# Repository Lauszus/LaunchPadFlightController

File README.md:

# LaunchPad Flight Controller
#### Developed by Kristian Sloth Lauszus, 2015-2020
_________

This is a flight controller used for a quadcopter in X-configuration.

It is written for the [Tiva C Series TM4C123G LaunchPad](http://www.ti.com/tool/EK-TM4C123GXL) running at 80 MHz.

More information can be found at the following blog posts: <http://blog.tkjelectronics.dk/2015/01/launchpad-flight-controller> and <http://blog.tkjelectronics.dk/2015/08/bachelors-thesis-launchpad-flight-controller>.

# Video demonstrations

Some video demonstrations of the flight controller can be seen at my [YouTube channel](https://www.youtube.com/playlist?list=PLRBI0ZWd8RfBnD1IZzrBdREjrzRAjWMqg).

# Report

The report I wrote for my Bachelor's thesis can be found in the [docs](docs) folder. The 3D model and Matlab code can be found in there as well.

# Features

* Rate mode, self level mode, heading hold and altitude hold
    - __AUX1:__ Use 3-POS switch for self level and heading hold. At first position both are off, at second position self level is on and at third position both are on
    - __AUX2:__ Use a 3-POS switch for altitude hold. Note that self level mode must be activated for altitude hold to work! At first position altitude hold is turned off, at second position altitude hold will use the distance measured using the sonar and/or LIDAR-Lite v3 and at the third position altitude hold will be using the altitude estimated using the barometer and accelerometer
* Store PID values, calibration values etc. in EEPROM
* Gyro, accelerometer & magnetometer calibration routine
    - Gyro is calibrated at startup
    - Accelerometer and magnetometer calibration routine can be activated in the code or by using the Android app
    - The magnetometer turns on the Blue LED while calibrating
        + Rotate flight controller slowly along all three axis
* Arm/disarm using rudder
* Status LEDs
* Supports CPPM receivers
* Gyro & accelerometer (MPU-6500 or MPU-9250)
* Magnetometer (HMC5883L or AK8963 (inside MPU-9250))
* Barometer (BMP180)
* Ultrasound sensor aka sonar (HC-SR04)
* [LIDAR-Lite v3](https://buy.garmin.com/en-US/US/p/557294)
    - Connect a 680 µF electrolytic capacitor from 5V to GND
* Optical flow sensor (ADNS3080)
* [Android application](https://github.com/Lauszus/LaunchPadFlightControllerAndroid)
* OneShot125 ESC support
* Buzzer feedback

# Current setup

* Motors: Dualsky 980kv
* ESC's: [Hobby King 20A ESC 3A UBEC (F-20A)](http://hobbyking.com/hobbyking/store/uh_viewItem.asp?idProduct=37253) - flashed with SimonK bs_nfet with OneShot125 and COMP_PWM = 1
* Propellers: 10x4.5
* Frame: [Hobby King Q450 V3 Glass Fiber Quadcopter Frame 450mm](http://hobbyking.com/hobbyking/store/__49725__Q450_V3_Glass_Fiber_Quadcopter_Frame_450mm_Integrated_PCB_Version.html)
* LiPo: [Turnigy 3300mAh 3S 30C Lipo Pack](http://hobbyking.com/hobbyking/store/uh_viewItem.asp?idProduct=35870)
* RX: [OrangeRX R615X](http://www.hobbyking.com/hobbyking/store/__46632__OrangeRx_R615X_Spektrum_JR_DSM2_DSMX_Compatible_6Ch_2_4GHz_Receiver_w_CPPM.html)
* TX: [Turnigy 9XR](http://www.hobbyking.com/hobbyking/store/__31544__Turnigy_9XR_Transmitter_Mode_2_No_Module_.html) flashed with OpenTX
* TX module: [OrangeRX 2.4GHz transmitter module](http://hobbyking.com/hobbyking/store/__24656__OrangeRX_DSMX_DSM2_2_4Ghz_Transmitter_Module_JR_Turnigy_compatible_.html)

# Pinout

| Pin  |        Connection       |   Hardware peripheral   |
|------|-------------------------|-------------------------|
| PA0  |         UART RX         |     U0RX (UART0 RX)     |
| PA1  |         UART TX         |     U0TX (UART0 TX)     |
| PA2  |         SPI CLK         |         SSI0CLK         |
| PA3  |         SPI SS          |         SSI0Fss         |
| PA4  |         SPI MISO        |         SSI0Rx          |
| PA5  |         SPI MOSI        |         SSI0Tx          |
| PA6  |           SCL           |         I2C1SCL         |
| PA7  |           SDA           |         I2C1SDA         |
| PB0* |       Bluetooth RX      |     U1RX (UART1 RX)     |
| PB1* |       Bluetooth TX      |     U1TX (UART1 TX)     |
| PB4  |         Motor 3         |         M0PWM2          |
| PB5  |         Motor 4         |         M0PWM3          |
| PB6  |         Motor 1         |         M0PWM0          |
| PB7  |         Motor 2         |         M0PWM1          |
| PC5  |        Sonar echo       |   WTimer0B (WT0CCP1)    |
| PC6  |        CPPM input       |   WTimer1A (WT1CCP0)    |
| PD2  |          Buzzer         |                         |
| PE0  |       Sonar trigger     |                         |
| PE1  |      ADNS3080 reset     |                         |
| PE2  |  MPU-6500/MPU-9250 INT  |                         |
| PE3  |       HMC5883L DRDY     |                         |
| PF0  |         Switch 1        |                         |
| PF1  |         Red LED         |                         |
| PF2  |        Blue LED         |                         |
| PF3  |        Green LED        |                         |
| PF4  |         Switch 2        |                         |

\* UART1 is connected to an HC-06 Bluetooth module running at a baudrate of 115200. __Not 5V tolerant!__, so make sure your Bluetooth module outputs 3.3 voltage level or use a logic level converter.

Furthermore WTimer1B is used to turn off motors if the connection to the RX is lost. SysTick counter is used for time basic time keeping functionality.

The MPU-6500/MPU-9250, HMC5883L, BMP180 and LIDAR-Lite v3 are connected via I<sup>2</sup>C if they are used.

All pins are defined in [src/Config.h](src/Config.h) and can be overriden by creating a file called "Config_custom.h" in the [src](src) directory allowing you to redefine the values.

# Notes

The motor layout follows the Naze32 in x-configuration i.e. motor 1 is bottom right, motor 2 is top right, motor 3 is bottom left and motor 4 is top left when looking from the back. Motor 1 and 4 should be spinning clockwise and motor 2 and 3 should be spinning counterclockwise.

Make sure that roll increases when tilting quadcopter to the right, pitch increases when pitching quadcopter upward and yaw increases when rotation quadcopter clockwise. This can be displayed using the graph menu in the [Android application](https://github.com/Lauszus/LaunchPadFlightControllerAndroid).

The flight controller is armed by having the throttle low and the rudder to the right. The flight controller is disarmed again by having the throttle low and the rudder to the left.

## Initial setup

1. Locate the line ```#define ONESHOT125 1``` in [PPM.c](src/PPM.c) and set line to 0 if your ESCs does not support OneShot125, if you are in doubt, then set the value to 0.
2. Configure the orientation of the MPU-9250/6500 and HMC5883L, so they corresponds to your setup. This is done inside ```mpu6500BoardOrientation``` and ```hmc5883lBoardOrientation``` in [MPU6500.c](src/MPU6500.c) and [HMC5883L.c](src/HMC5883L.c) respectively.
    * The x-axis should be facing forward, the y-axis should be facing to the right and the z-axis should be facing downward. Typically the axis is indicated on the breakout board for the sensor.

### Calibrating the ESCs

__WARNING:__ Take propellers OFF when testing and calibrating ESCs!!

In order calibrate the ESCs you need to do the following procedure:

1. Power up the board while holding down both hardware switches. The blue LED will come on, indicating that the ESCs will be calibrated at next power up.
2. Turn the board off by disconnecting the battery.
3. Now apply power while holding down the two hardware switches. The board will send out the maximum and minimum pulses to the ESCs and thus calibrating them. When the ESC calibration is done the blue LED will be turned off and a long beep will be played.

The calibration is canceled if the buttons are not held down during the whole procedure or the reset is not performed by a power on reset. The former allows the user to cancel the calibration at any time by releasing the switches and the latter prevents the user from accidentally resetting the board without also resetting the ESCs, for instance by pressing the reset button on the board.

### Calibrating accelerometer and magnetometer

The last step is to calibrate the accelerometer and magnetometer. The accelerometer is calibrated by putting the quadcopter horizontal and activating the calibration routine via the [Android application's](https://github.com/Lauszus/LaunchPadFlightControllerAndroid) settings menu. It is important that the quadcopter is kept still while running the accelerometer calibration routine. When the calibration is done a long beep will be played using the onboard buzzer.

The magnetometer calibration routine is activated similar to the accelerometer by using the [Android application](https://github.com/Lauszus/LaunchPadFlightControllerAndroid). The blue LED will turn on, indicating that the calibration procedure is activated. Now rotate the quadcopter along all three axis slowly in order to find the minimum and maximum values. The user has 30 seconds to rotate the quadcopter. Once the calibration is done the blue LED will be turned off and a long beep will be played.

It is a good idea to confirm that the estimated angles are all correct by using the graph menu in the [Android application](https://github.com/Lauszus/LaunchPadFlightControllerAndroid).

There is no need to calibrate the gyroscope, as this is done at every startup.

### RX

The minimum and maximum receiver values are hardcoded in [src/Config.h](src/Config.h) and might need to be adjusted as well.

# Android application

The Android source code is available at the following repository: <https://github.com/Lauszus/LaunchPadFlightControllerAndroid>.

# GUI

A simple GUI can be found inside the [GUI](GUI) directory. It can be used to visualise the orientation of the flight controller.

# Build instructions

## PlatformIO

[PlatformIO](http://platformio.org) is a cross-platform build system, which makes it easy to compile and upload the code on both Windows, Linux and Mac. This is the recommended way to compile the code for novice users.

Please follow these instructions in order to install Python 2.7 and PlatformIO: <http://docs.platformio.org/en/latest/installation.html>.

On Windows be sure to select "Add python.exe to Path" when installing Python 2.7.

Open a terminal (search for ```cmd.exe``` on Windows) and navigate to the root of the project:

```bash
cd LaunchPadFlightController
```

Now compile the code:

```bash
platformio run
```

The program should now be compiled.

In order to upload the code simply type:

```bash
platformio run -t upload
```

I recommend installing the [PlatformIO IDE](http://platformio.org/get-started/ide?install) if using PlatformIO.

## Keil µVision IDE 5

In order to built this project you need to download Keil µVision IDE 5 and then simply open the [project file](LaunchPadFlightController.uvprojx).

## Manual installation

In order to built this project you will need to use [Make](http://www.gnu.org/software/make/).

First download and install [gcc-arm-none-eabi](https://launchpad.net/gcc-arm-embedded/4.8/4.8-2014-q3-update) and then install [lm4tools](https://github.com/utzig/lm4tools).

lm4tools can be installed like so:

```bash
$ git clone https://github.com/utzig/lm4tools.git
$ make -C lm4tools/lm4flash all
$ sudo cp lm4tools/lm4flash/lm4flash /usr/bin/
```

If you are on a Mac, I recommend installing gcc-arm-none-eabi using [Homebrew](http://brew.sh) like so:

```bash
$ brew tap PX4/homebrew-px4
$ brew update
$ brew install gcc-arm-none-eabi
```

Now simply compile the code by navigating to the [src](src) and running the following command:

```bash
make
```

And to upload the code:

```bash
make flash
```

Some information on configuring Eclipse for use with this project can be the [Wiki](https://github.com/Lauszus/LaunchPadFlightController/wiki).

### Hardware debugging using OpenOCD

OpenOCD can be installed via [Homebrew](http://brew.sh) as well:

```bash
$ brew install openocd
```

Now run the following commands:

```bash
$ openocd --file /usr/local/share/openocd/scripts/board/ek-tm4c123gxl.cfg

$ arm-none-eabi-gdb gcc/LaunchPadFlightController.axf
(gdb) target extended-remote :3333
(gdb) monitor reset halt
(gdb) load
(gdb) monitor reset init
```

More information regarding hardware debugging can be found at the [Wiki](https://github.com/Lauszus/LaunchPadFlightController/wiki/Hardware-Debugging-In-Eclipse).

# Credits

A lot of the inspiration for this code came from [Cleanflight](https://github.com/cleanflight/cleanflight) and other open source flight controller projects.

For more information send me an email at <lauszus@gmail.com>.

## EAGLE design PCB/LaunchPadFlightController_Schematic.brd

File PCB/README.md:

# LaunchPad Flight Controller
#### Developed by Kristian Sloth Lauszus, 2015
_________

This is the design files for the PCB that is designed to plug onto the headers on the Tiva LaunchPad. You can order the PCB directly from the following link: <https://www.oshpark.com/shared_projects/9DC5cp8e>.

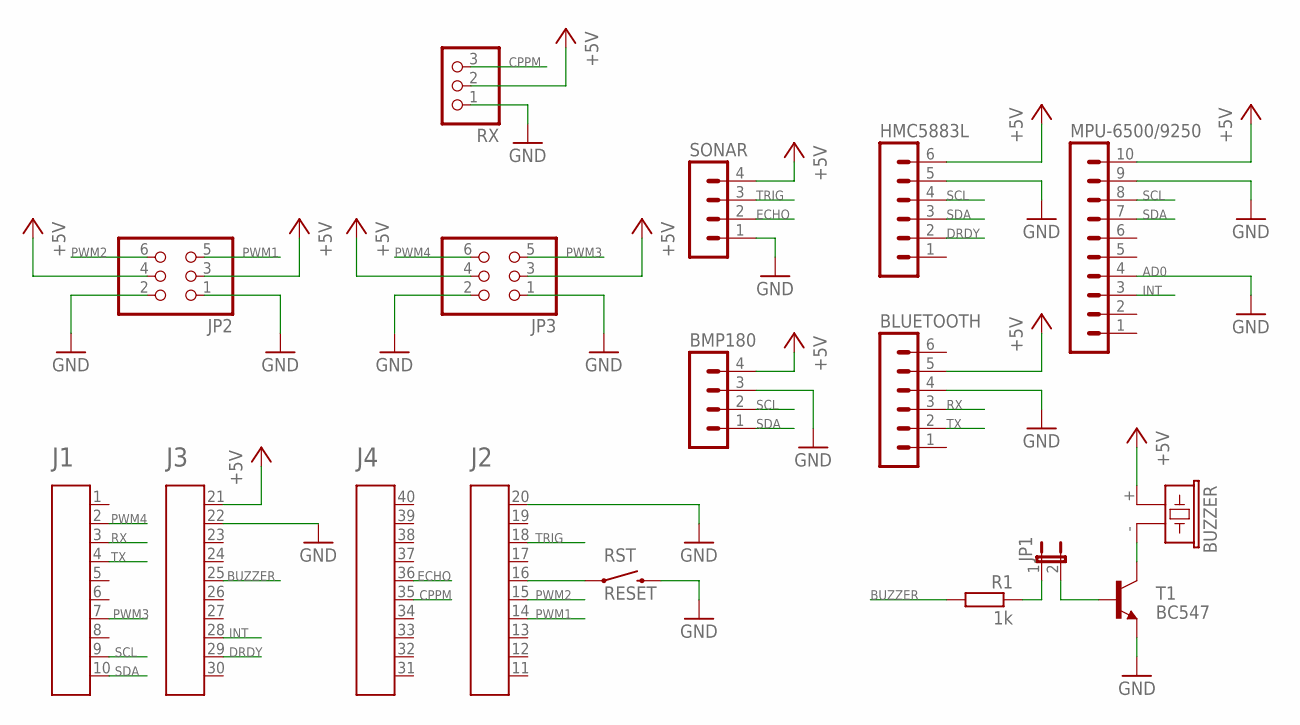
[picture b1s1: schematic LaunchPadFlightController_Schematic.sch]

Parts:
A1: HEADER4X10-BOOSTERPACK; 4X10-BOOSTERPACK
BLUETOOTH: MA06-1
BMP180: MA04-1
BUZZER: F/CM12P
HMC5883L: MA06-1
JP1: JP1E; JP1
JP2, JP3: PINHD-2X3; 2X03
MPU-6500/9250: MA10-1
R1: 1k; 0207/10
RST: RESET; TACTILE-PTH-EZ
RX: PINHD-1X3; 1X03
SONAR: MA04-1
T1: BC547; TO92

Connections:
+5V: A1.21, BLUETOOTH.5, BMP180.4, BUZZER.+ (1), HMC5883L.6, JP2.3, JP2.4, JP3.3, JP3.4, MPU-6500/9250.10, RX.2, SONAR.4
BUZZER: A1.25, R1.2
CPPM: A1.35, RX.3
DRDY: A1.29, HMC5883L.2
ECHO: A1.36, SONAR.2
GND: A1.20, A1.22, BLUETOOTH.4, BMP180.3, HMC5883L.5, JP2.1, JP2.2, JP3.1, JP3.2, MPU-6500/9250.4, MPU-6500/9250.9, RST.3 (2), RX.1, SONAR.1, T1.1 (E)
INT: A1.28, MPU-6500/9250.3
unnamed: A1.16, RST.1
unnamed: JP1.1, R1.1
unnamed: JP1.2, T1.2 (B)
unnamed: BUZZER.- (2), T1.3 (C)
PWM1: A1.14, JP2.5
PWM2: A1.15, JP2.6
PWM3: A1.7, JP3.5
PWM4: A1.2, JP3.6
RX: A1.3, BLUETOOTH.3
SCL: A1.9, BMP180.2, HMC5883L.4, MPU-6500/9250.8
SDA: A1.10, BMP180.1, HMC5883L.3, MPU-6500/9250.7
TRIG: A1.18, SONAR.3
TX: A1.4, BLUETOOTH.2

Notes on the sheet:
AD0

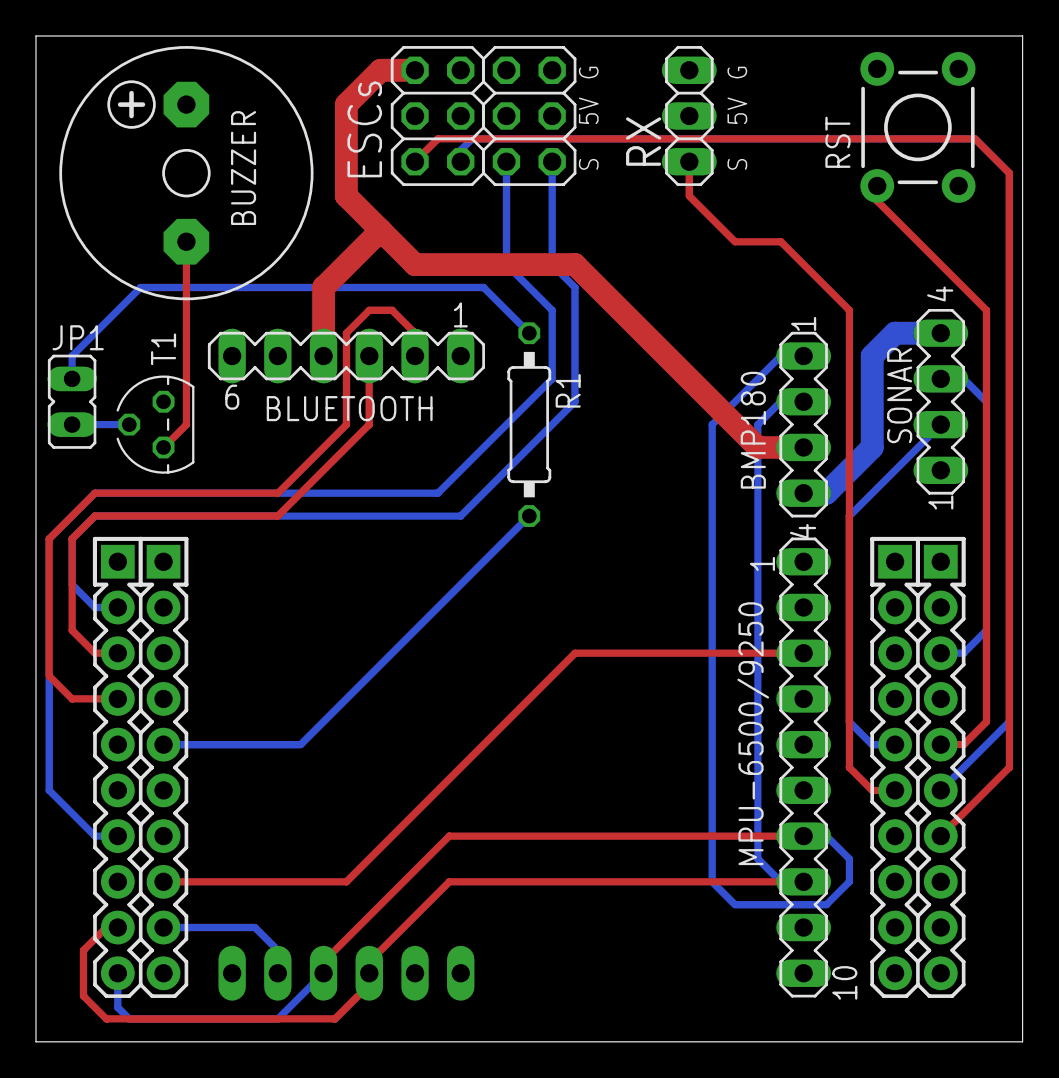
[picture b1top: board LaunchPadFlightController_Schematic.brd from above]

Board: 2 copper layers, 54.8 x 55.9 mm, 14 parts (1 on the bottom side), 20 nets.

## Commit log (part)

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2015-04-02 Check number of bytes available before calling UARTPeek1, as bytes might be received after UARTPeek1 is called
    There is still a slight change that data is received between the two functions, but it is very unlikely and the checksum should prevent the data to be actually stored
2015-04-05 Moved local variables into .c file
    Also save timer load value in variable
2015-04-05 Fix typo
2015-04-06 Can now set Angle Kp, maximum angle inclination and stick scaling
2015-04-08 Added buzzer code
2015-04-17 Updated TODO list
2015-04-17 Multiply PID values by a higher value to allow finer adjustments
2015-04-17 Take average of several deltas in D-term calculation
    Inspired by: https://github.com/cleanflight/cleanflight/blob/004dd0daaf5c89412064253f8549ebe1bfc03f99/src/main/flight/pid.c#L721-L732
2015-04-17 Beep for 1s after accelerometer calibration
2015-04-18 Can now calibrate accelerometer and restore default configuration values
    Nothing was changed in EEPROM.c except order of functions
2015-04-18 Only save Kp, Ki, Kd and integration limit in EEPROM
    There is no need to save the rest in the EEPROM
2015-04-18 Enabled OneShot125
    This allows the ESC output to be in sync with IMU reading.
    Note that motor update code was moved inside IMU reading code and some other code were rearranged - nothing else was changed in main.c
2015-04-18 Added list of current features
2015-04-18 Escape asterisk symbol
2015-04-19 Limit other motors if one reaches maximum
    Got code from: https://github.com/cleanflight/cleanflight/blob/78a4476506c06315d7296a010a2c7ba003146b44/src/main/flight/mixer.c#L680-L695
2015-04-22 Make sure UART_DEBUG is defined before printing debug information in RX.c
2015-04-22 Switch to Keil µVision IDE 5
2015-04-23 Improved self level mode
    Use rotation matrices to rotate accelerometer vector and use LPF on accelerometer values
    Inspired by: https://github.com/cleanflight/cleanflight/blob/78a4476506c06315d7296a010a2c7ba003146b44/src/main/flight/imu.c
    Doesn't seem like I can use my Kalman filter as it is, as it written for a 1-axis application
    Note I increase optimisation level to -O3 as well, as it generated wrong code at -O0
2015-04-23 Added GUI application used to visualise orientation of flight controller
    For now one has to manually set: https://github.com/Lauszus/LaunchPadFlightController/blob/2555673079926c2b7602c29a05033d63cc0e9e17/src/IMU.c#L85 to 1.
2015-04-24 Initial support for magnetometer (HMC5883L)
2015-04-24 Fix indentation
    No new code was added
2015-04-24 Moved magnetometer calibration routine into driver
2015-04-24 Send out angle information every 10 ms
    Also removed some unused code
2015-04-25 Don't hardcode register value, use name instead
2015-04-25 Added some information about Bluetooth module and magnetometer calibration routine
2015-04-25 Implemented heading hold mode
    Also found bug where angle mode were actually toggled back and forth instead of staying in angle mode
2015-04-27 Added credits
2015-04-28 Set accelerometer and gyroscope scale inside MPU-6500 driver
    This should make it easier to add support for other sensors in the future
2015-04-28 Make sure heading code is only compiled when magnetometer is actually used
    Also moved some variables into the relevant part of the code instead of being defined in the top
2015-04-28 New default angleKp value
2015-05-03 Fixed link to Android application and Cleanflight
2015-05-23 Almost got PlatformIO working
    Need to set reset handler and get it to compile the .S file.
2015-05-23 Initialise struct
    Fixes: "warning: 'mag_total.<U9098>.X' may be used uninitialized in this function [-Wmaybe-uninitialized]"
2015-05-23 Set optimisation level to -O3
2015-05-24 Added UART handlers to vector table
    Also increased stack size to match old one in startup_rvmdk.S
2015-05-25 Hardcode length of sensor buffer, so it compiles when using gcc
2015-05-25 math library should be lowercase
2015-05-25 New headKp value
2015-05-25 Move all rules onto one line
2015-05-25 Use object list to automatically build all object files
2015-05-25 Remove everything related to Kalman filter, as it is not used
2015-05-25 Don't hardcode target name
2015-05-25 Added space between variable name and value
2015-05-25 Print sizes of sections inside binary file
2015-05-25 Ignore Eclipse project files
2015-05-26 Added GDB commands notes
2015-05-26 Forgot to add '$' sign before commands
2015-05-26 Typo
2015-05-26 Normalize all the line endings
2015-05-26 Allow flags to be overridden by command line
    I use this with Eclipse
2015-05-26 Use state machine instead of delay, so the BMP180 driver can actually be used
2015-05-26 Also build versions with and without magnetometer and barometer enabled
2015-05-26 Set job manually, as matrix did not work
2015-05-26 Use one state less in BMP180 driver
2015-05-27 Added double-promotion and unsafe-loop-optimizations warnings
2015-05-27 Moved sonar to different pins
2015-05-27 Use temperature from BMP180 to compensate for the difference in speed of sound in air
2015-05-27 Implement altitude hold using sonar
2015-05-27 Return sonar distance in mm instead
2015-05-27 Reset alt hold terms separately
2015-05-27 There is no need to check if we should trigger sonar that often, so it is limited to the update rate of IMU
2015-05-27 Take care of timer overflow in a better way
2015-05-27 Added code, so sonar distance can easily be printed for debugging
2015-05-27 Don't turn on buzzer if timer overflows in DEBUG mode
2015-05-28 Only use '__attribute__((packed))' if it is actually needed in order to reduce code size
    Also added static keyword to some structs inside Bluetooth.c
2015-05-28 Added take off sequence
    Will take off and stay at 1m
2015-05-28 Added some comments in sonar driver
2015-05-28 Can now adjust height when in altitude mode
2015-05-28 Surround heading mode and altitude mode variables in #if statements
2015-05-28 Forgot to around altitudeMode variable in #if statement
2015-05-29 Not all code is released under GPL like all the TI files
2015-05-29 Altitude hold wan't properly reset
2015-05-29 Compensate for 3D tilt angle in sonar
2015-05-29 Just save US_ROUNDTRIP_CM as an integer, as mm resolution is more than what the sensor is capable of anyway
    Also updated some comments
2015-05-29 Moved altitude hold code into it's own source files
2015-05-29 Moved sonar code into altitude code as well
2015-05-29 Save maxAngleInclinationSonar in EEPROM
    Also made the it able to compile when USE_SONAR is 0
2015-05-29 Don't hardcode sonar minimum and maximum distance
2015-05-30 Fix so Bluetooth code compiles when no magnetometer is used
2015-05-30 Rename altitude hold file
2015-05-30 Surrond uartstdio.h include in if statements, so it throws an error if one try to print anyway
2015-05-30 Just pass temperature directly to sonar driver
2015-05-31 Make msg struct a local variable
2015-06-01 Added source files to Keil project file
2015-06-07 Removed unused include
2015-06-08 Go between 10cm to 50cm when checking altitude step response
2015-06-08 Show logging status using blue LED
2015-06-08 Set message length after checking if pointer is valid
2015-06-09 Added some more links about rotation matrices
2015-06-10 Updated Keil project file
2015-06-14 Added Android device art screenshots
2015-06-14 Added unused-parameter warning
2015-06-14 Use a different define variable to activate each step response code
2015-06-14 Rename variable, so it becomes more clear that it is in fact just a P controller
2015-06-15 There is no need to set altHoldSetPoint and altHoldInitialThrottle twice
2015-06-16 Deal with sonar overflow in a better way
    This is already dealt with in the altitude hold driver
2015-06-17 Suppress unused parameter warning
2015-06-17 Subtract sonar offset from all altitude estimates
2015-06-17 Renamed variable, so it is clear that it is the inertial frame
2015-06-18 Fixed comments and variable names as it is in the body frame and the altitude estimation should rotate it back into the inertial frame
2015-06-18 Added TODO
2015-06-18 Fixed comment
2015-06-18 Yaw angle is already inverted
2015-06-19 Magnetometer can also be calibrated using Android app
2015-06-21 Re-add overflow timer check in sonar driver
    I suspect that this is needed as the timer is operating as a 16-bit timer
2015-06-21 Renamed getAltitudeHold to getAltitude, so it better reflects what the code actually do
2015-07-06 Initial support for altitude hold based on barometer
2015-07-18 Fixed typo in BMP180 driver
2015-07-18 Added AK8963 driver
    The AK8963 is inside the MPU-9250
2015-07-18 Use the orientation function for the MPU-6500 inside the AK8963 driver
2015-07-18 Make getMagData return if new data is read
    This simplifies the mag calibration function
2015-07-23 Fixed debug print
2015-07-28 Cast sensor data explicitly to int16_t
    This was causing issues in the calibrateSensor function on some compilers, it was just done in the rest of the code to be future proof
2015-07-28 Stay in endless while loop if HMC5883L is detected, but self test fails
2015-07-29 Moved building instructions, GUI and Android sections down in the readme
2015-07-29 Added information about the report I wrote
2015-08-17 Print the type of magnetometer found inside high-level magnetometer driver instead
    LEDs had to be initialised before magnetomer was initialised, as the Blue LED will turn on in case no magnetometer is detected
2015-08-17 Added MPU-9250 to pinout table
2015-08-21 Uploaded PCB files
    Can be ordered here: https://oshpark.com/profiles/Lauszus
2015-08-23 Updated copyright header
2015-08-24 Added link to blog post
2015-09-07 Increased resolution of ADNS-3080 to 1600 counts per inch
    Also increased delay between printing pixel data to 1500 ms
2015-09-07 Always print leading with leading zeroes if value is less that two characters
2015-10-09 Added link to Wiki regarding hardware debugging
2016-01-18 Fixed a bunch of warnings
2016-04-22 Added changes to Keil configuration and file name issue.
2016-04-22 GUI file ajusted to Windows.
2016-04-23 MPU mounting direction corrected.
2016-04-26 msg_t already provide the length of the message
2016-04-28 Added READMEs for both the PCB and docs directories
2017-01-10 Added initial support for LIDAR-Lite v3
    See: https://buy.garmin.com/en-US/US/p/557294
2017-01-13 Do not use the mode control pin, as we would be polling it anyway
    It is always very noise and will require a 1k pull-down and a 1 pF capacitor to GND
2017-01-13 Renamed maximum angle inclination variable, as it is now both used for the Sonar and LIDAR-Lite v3
2017-02-07 The Android app is now on the Google Play store
2017-03-06 Use NED-coordinate system
2017-03-14 Added notes on how the low pass filters coefficients should be calculated
2017-03-14 Rewrite all low-pass filters, so they are all on the same form and depend on dt
2017-03-15 Subtract 1g before the z-acceleration is inverted
2017-03-19 Forgot to add check for USE_LIDAR_LITE build flag in main at several places
2017-03-28 Print configurable build flags when building the code
2017-04-07 The cutoff frequency was about 150 Hz when using the moving average low pass filter
    The Kd constant should also be only one third of what is was before
    See: http://dsp.stackexchange.com/questions/9966/what-is-the-cut-off-frequency-of-a-moving-average-filter and https://www.dsprelated.com/showthread/comp.dsp/155807-1.php
2017-04-10 Updated note in altitude hold
2017-04-11 Do not transmit \r when sending \n in uartstdio
2017-04-12 Use eclint to check coding style
2017-04-13 Make SPI driver more generic
2017-04-14 Move most pin definitions into Config.h, so they can easily be modified by creating a file called Config_custom.h
    The SPI, I2C and PPM hardware drivers are still hardcoded
2017-04-14 Automatically configure the Bluetooth module in case it is the first time it is powered on
2017-04-17 Build project using PlatformIO
2017-05-03 Use one SPI function for all transactions
2017-05-03 Use PE1 for the ADNS3080 instead
2017-05-04 Send data from ADNS3080 as raw bytes
2017-05-07 Ignore PyCharm project directory
2017-05-11 Added note about motor spinning direction
2017-05-11 Explicit convert to 16-bit values
    I forgot to do it in this commit: https://github.com/Lauszus/LaunchPadFlightController/commit/f52ead3033a989c0a1d27167dc0057d67711f3dc
2017-05-18 Block comment
2020-04-11 Removed finished TODO
2020-04-11 Updated PlatformIO build script, so it matches the Makefile
